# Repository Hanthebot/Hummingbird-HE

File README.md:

# Hummingbird-HE

Hall-effect variant of Hummingbird keyboard.

32 keys with detachable extra thumb key, otherwise the same layout as Rufous.

Firmware / configurator to be added.

## Licenses
All code under firmware folder follows GPL v3.

Webapp / HW is MIT license.

## Disclaimer
Webapp and firmware modification were vibe coded.

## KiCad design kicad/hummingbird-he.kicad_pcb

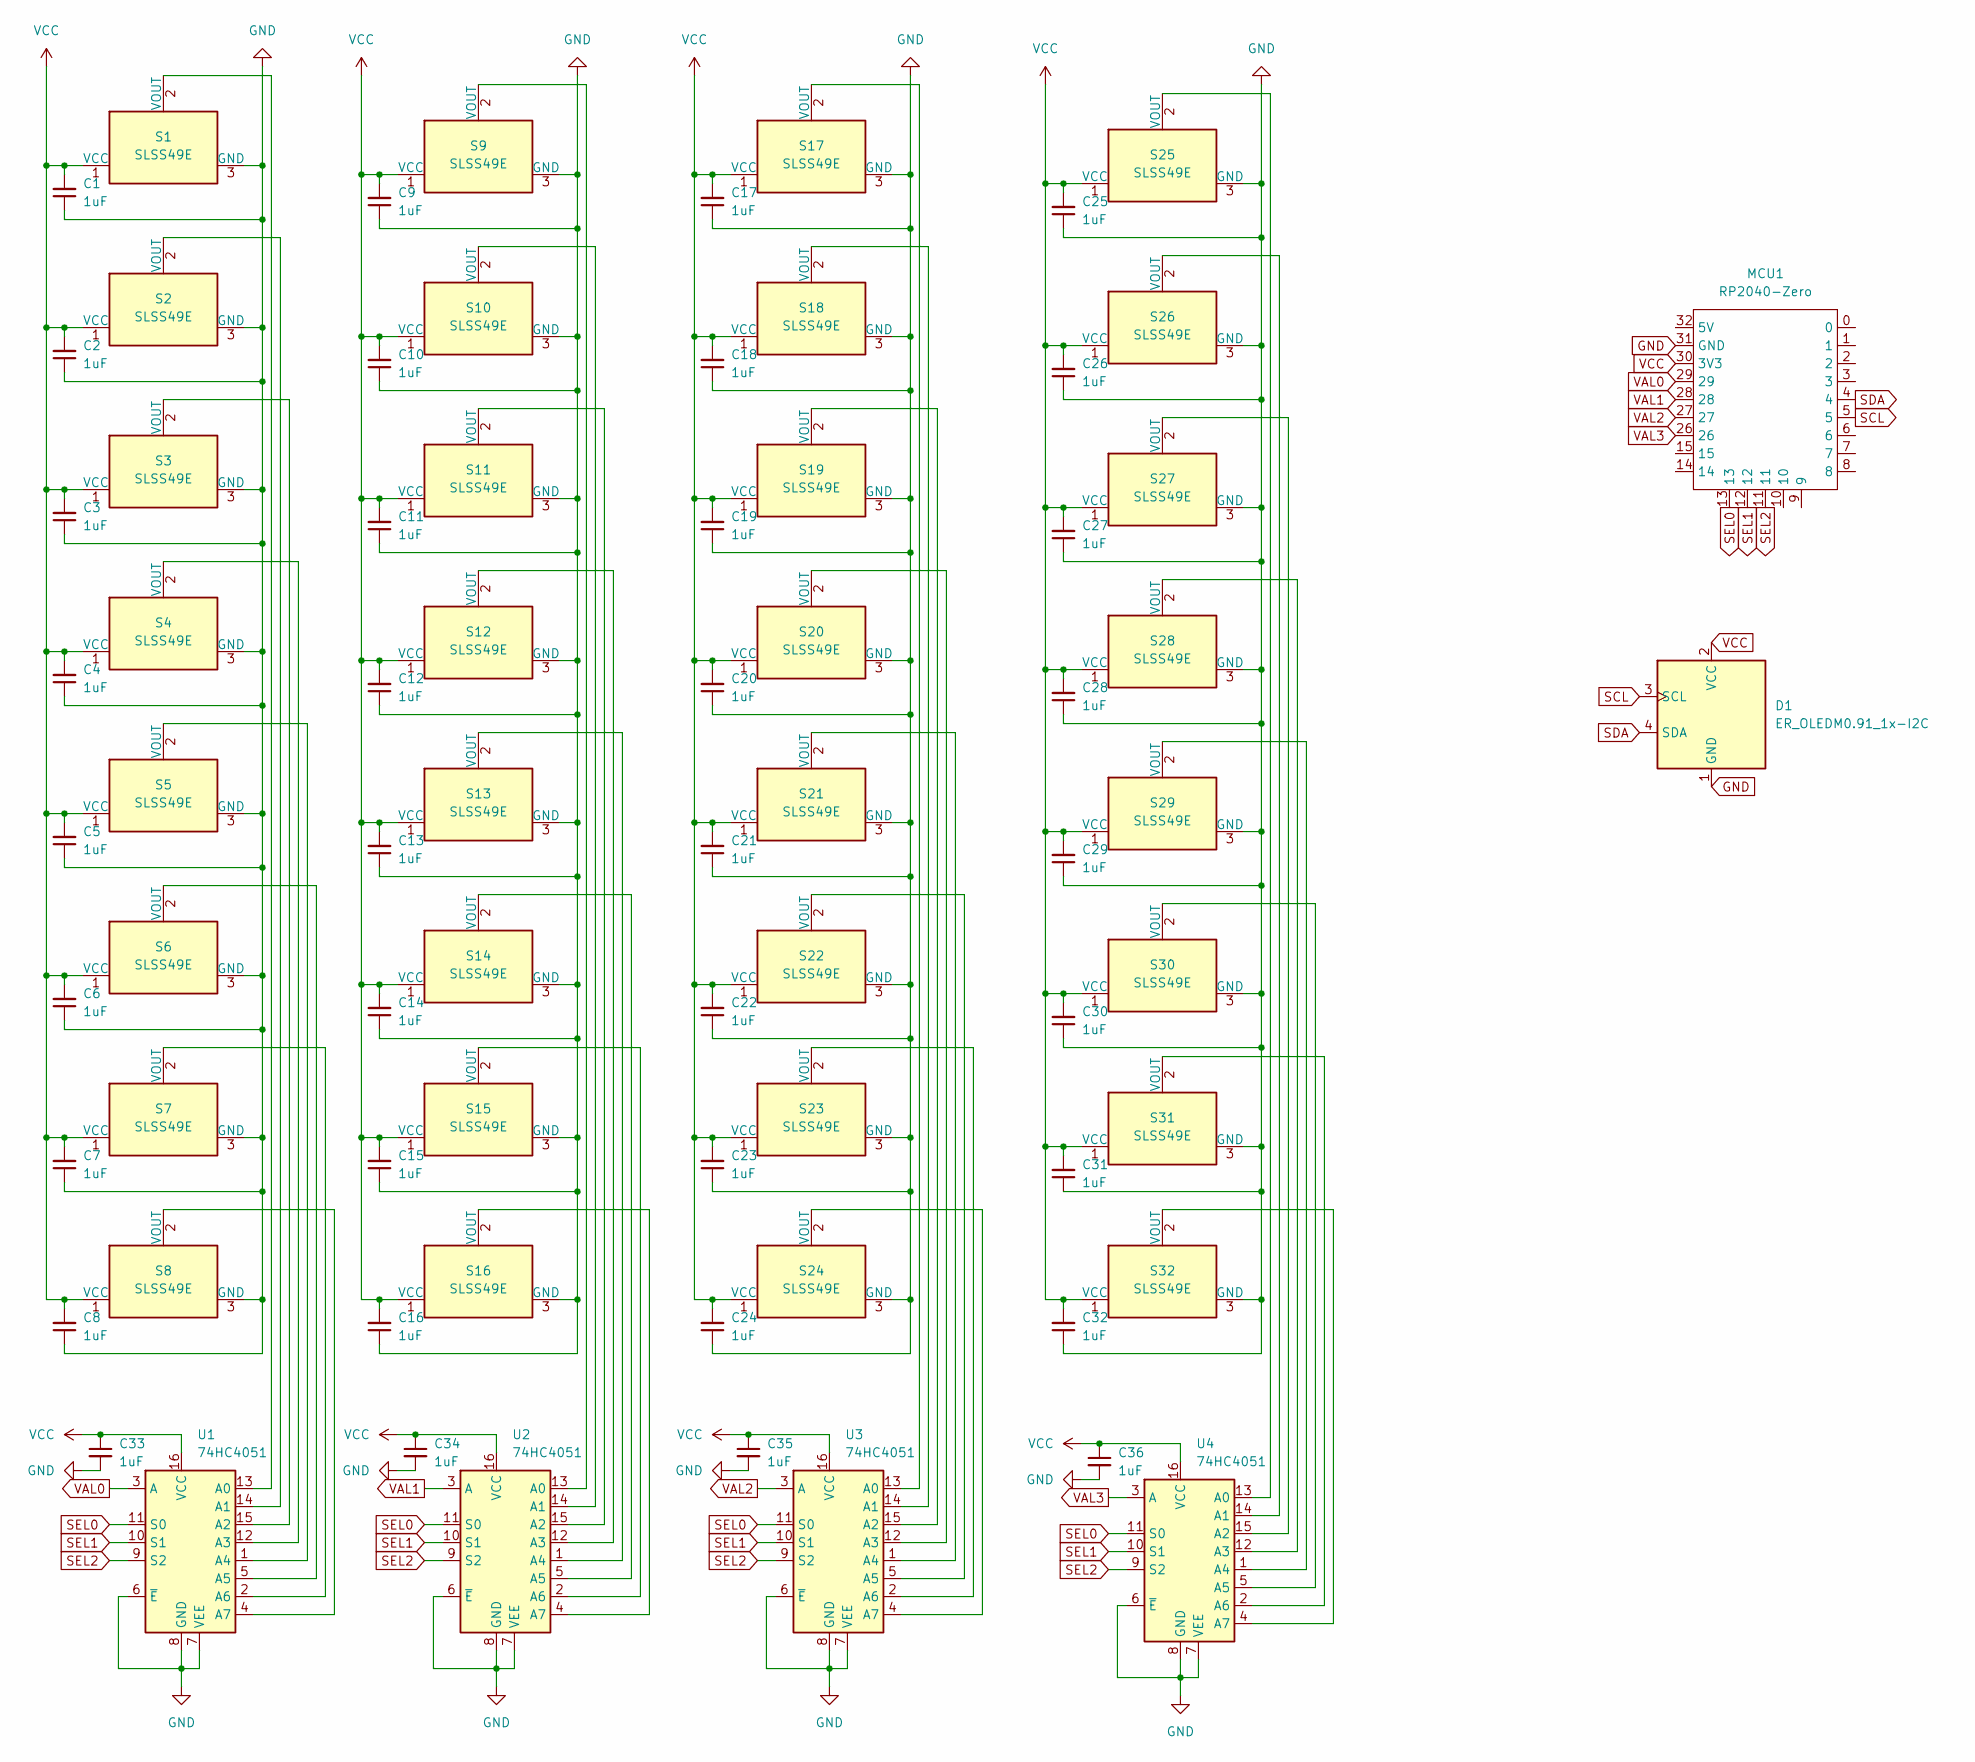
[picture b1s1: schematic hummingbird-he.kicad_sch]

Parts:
C1, C2, C3, C4, C5, C6, C7, C8, C9, C10, C11, C12, C13, C14, C15, C16, C17, C18, C19, C20, C21, C22, C23, C24, C25, C26, C27, C28, C29, C30, C31, C32, C33, C34, C35, C36: 1uF; C_0805_2012Metric_Pad1.18x1.45mm_HandSolder
D1: ER_OLEDM0.91_1x-I2C
MCU1: RP2040-Zero; RP2040-Zero-RESIZED
S1, S2, S3, S4, S5, S6, S7, S8, S9, S10, S11, S12, S13, S14, S15, S16, S17, S18, S19, S20, S21, S22, S23, S24, S25, S26, S27, S28, S29, S30, S31, S32: SLSS49E; HE-Switch-1U
U1, U2, U3, U4: 74HC4051; SOIC-16_3.9x9.9mm_P1.27mm

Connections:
GND: C1.1, C2.1, C3.1, C4.1, C5.1, C6.1, C7.1, C8.1, C9.1, C10.1, C11.1, C12.1, C13.1, C14.1, C15.1, C16.1, C17.1, C18.1, C19.1, C20.1, C21.1, C22.1, C23.1, C24.1, C25.1, C26.1, C27.1, C28.1, C29.1, C30.1, C31.1, C32.1, C33.2, C34.2, C35.2, C36.2, D1.1 (GND), MCU1.31 (GND), S1.3 (GND), S2.3 (GND), S3.3 (GND), S4.3 (GND), S5.3 (GND), S6.3 (GND), S7.3 (GND), S8.3 (GND), S9.3 (GND), S10.3 (GND), S11.3 (GND), S12.3 (GND), S13.3 (GND), S14.3 (GND), S15.3 (GND), S16.3 (GND), S17.3 (GND), S18.3 (GND), S19.3 (GND), S20.3 (GND), S21.3 (GND), S22.3 (GND), S23.3 (GND), S24.3 (GND), S25.3 (GND), S26.3 (GND), S27.3 (GND), S28.3 (GND), S29.3 (GND), S30.3 (GND), S31.3 (GND), S32.3 (GND), U1.6 (~E), U1.7 (VEE), U1.8 (GND), U2.6 (~E), U2.7 (VEE), U2.8 (GND), U3.6 (~E), U3.7 (VEE), U3.8 (GND), U4.6 (~E), U4.7 (VEE), U4.8 (GND)
unnamed: S1.2 (VOUT), U1.13 (A0)
unnamed: S2.2 (VOUT), U1.14 (A1)
unnamed: S3.2 (VOUT), U1.15 (A2)
unnamed: S4.2 (VOUT), U1.12 (A3)
unnamed: S5.2 (VOUT), U1.1 (A4)
unnamed: S6.2 (VOUT), U1.5 (A5)
unnamed: S7.2 (VOUT), U1.2 (A6)
unnamed: S8.2 (VOUT), U1.4 (A7)
unnamed: S9.2 (VOUT), U2.13 (A0)
unnamed: S10.2 (VOUT), U2.14 (A1)
unnamed: S11.2 (VOUT), U2.15 (A2)
unnamed: S12.2 (VOUT), U2.12 (A3)
unnamed: S13.2 (VOUT), U2.1 (A4)
unnamed: S14.2 (VOUT), U2.5 (A5)
unnamed: S15.2 (VOUT), U2.2 (A6)
unnamed: S16.2 (VOUT), U2.4 (A7)
unnamed: S17.2 (VOUT), U3.13 (A0)
unnamed: S18.2 (VOUT), U3.14 (A1)
unnamed: S19.2 (VOUT), U3.15 (A2)
unnamed: S20.2 (VOUT), U3.12 (A3)
unnamed: S21.2 (VOUT), U3.1 (A4)
unnamed: S22.2 (VOUT), U3.5 (A5)
unnamed: S23.2 (VOUT), U3.2 (A6)
unnamed: S24.2 (VOUT), U3.4 (A7)
unnamed: S25.2 (VOUT), U4.13 (A0)
unnamed: S26.2 (VOUT), U4.14 (A1)
unnamed: S27.2 (VOUT), U4.15 (A2)
unnamed: S28.2 (VOUT), U4.12 (A3)
unnamed: S29.2 (VOUT), U4.1 (A4)
unnamed: S30.2 (VOUT), U4.5 (A5)
unnamed: S31.2 (VOUT), U4.2 (A6)
unnamed: S32.2 (VOUT), U4.4 (A7)
SCL: D1.3 (SCL), MCU1.5
SDA: D1.4 (SDA), MCU1.4
SEL0: MCU1.13, U1.11 (S0), U2.11 (S0), U3.11 (S0), U4.11 (S0)
SEL1: MCU1.12, U1.10 (S1), U2.10 (S1), U3.10 (S1), U4.10 (S1)
SEL2: MCU1.11, U1.9 (S2), U2.9 (S2), U3.9 (S2), U4.9 (S2)
VAL0: MCU1.29, U1.3 (A)
VAL1: MCU1.28, U2.3 (A)
VAL2: MCU1.27, U3.3 (A)
VAL3: MCU1.26, U4.3 (A)
VCC: C1.2, C2.2, C3.2, C4.2, C5.2, C6.2, C7.2, C8.2, C9.2, C10.2, C11.2, C12.2, C13.2, C14.2, C15.2, C16.2, C17.2, C18.2, C19.2, C20.2, C21.2, C22.2, C23.2, C24.2, C25.2, C26.2, C27.2, C28.2, C29.2, C30.2, C31.2, C32.2, C33.1, C34.1, C35.1, C36.1, D1.2 (VCC), MCU1.30 (3V3), S1.1 (VCC), S2.1 (VCC), S3.1 (VCC), S4.1 (VCC), S5.1 (VCC), S6.1 (VCC), S7.1 (VCC), S8.1 (VCC), S9.1 (VCC), S10.1 (VCC), S11.1 (VCC), S12.1 (VCC), S13.1 (VCC), S14.1 (VCC), S15.1 (VCC), S16.1 (VCC), S17.1 (VCC), S18.1 (VCC), S19.1 (VCC), S20.1 (VCC), S21.1 (VCC), S22.1 (VCC), S23.1 (VCC), S24.1 (VCC), S25.1 (VCC), S26.1 (VCC), S27.1 (VCC), S28.1 (VCC), S29.1 (VCC), S30.1 (VCC), S31.1 (VCC), S32.1 (VCC), U1.16 (VCC), U2.16 (VCC), U3.16 (VCC), U4.16 (VCC)

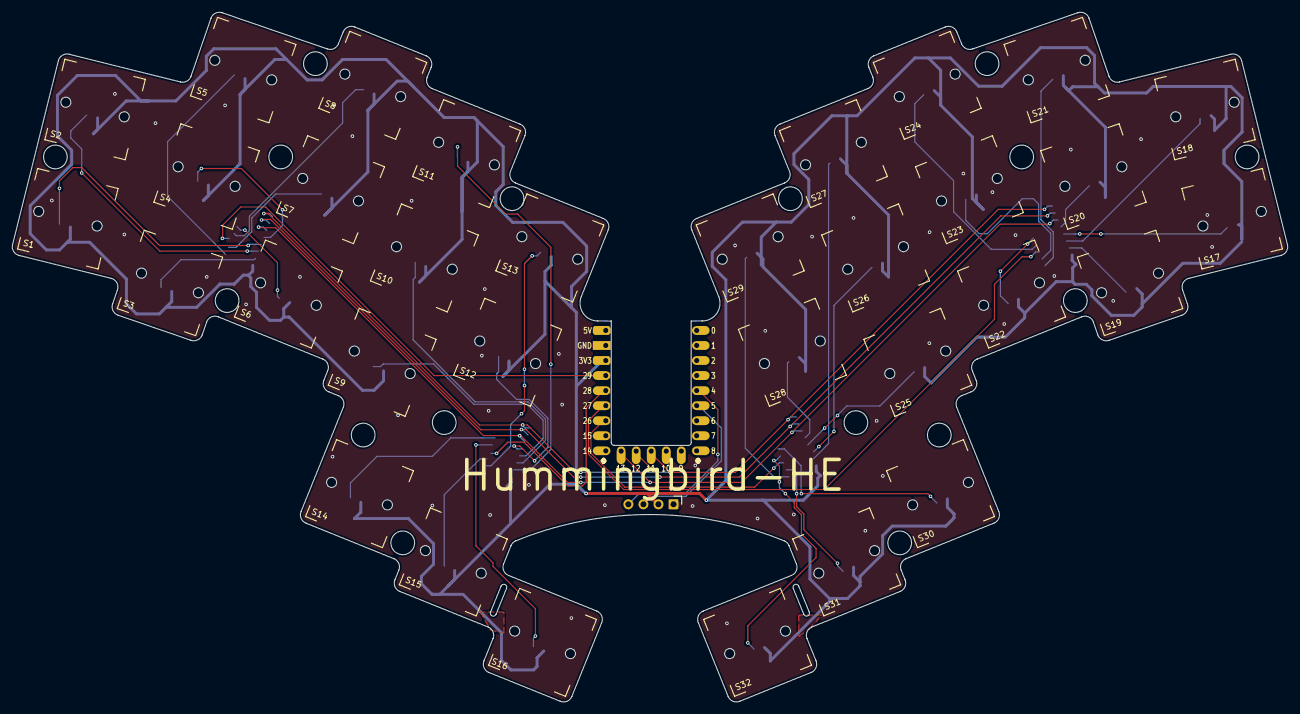
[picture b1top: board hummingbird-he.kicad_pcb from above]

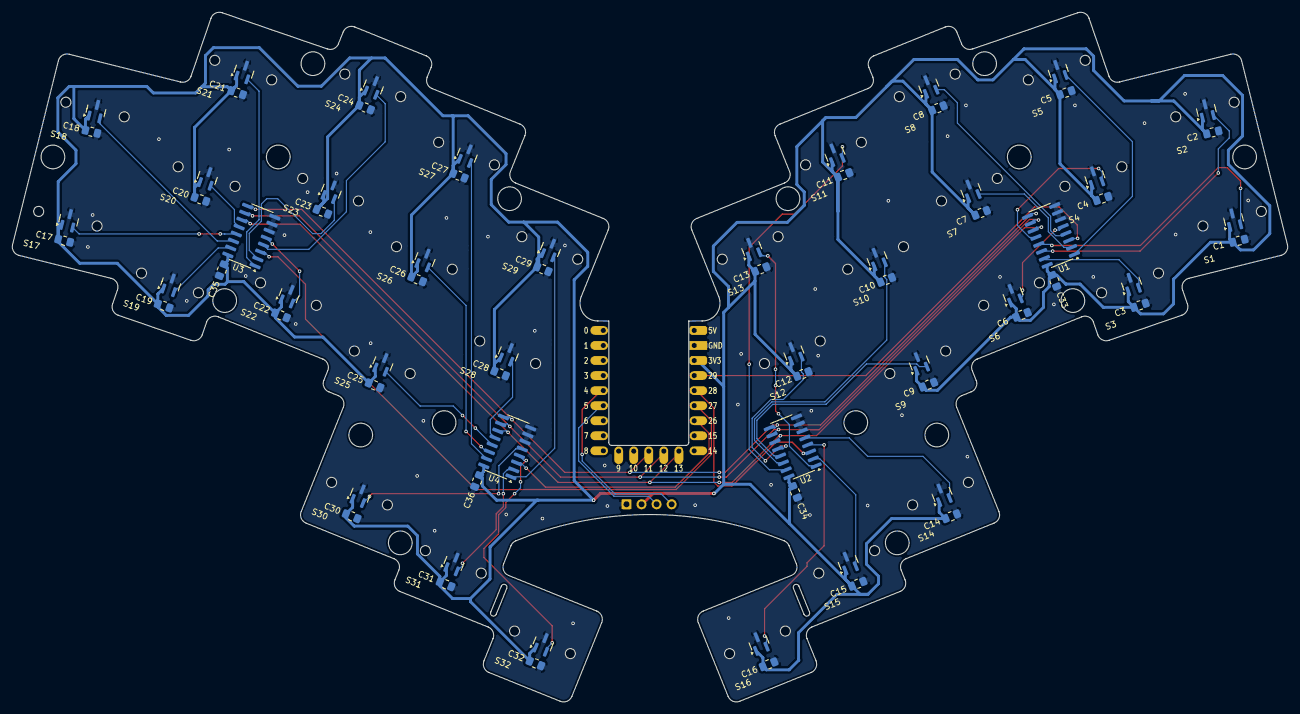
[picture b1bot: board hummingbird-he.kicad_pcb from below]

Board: 2 copper layers, 215.3 x 116.4 mm, 74 parts (40 on the bottom side), 43 nets.
